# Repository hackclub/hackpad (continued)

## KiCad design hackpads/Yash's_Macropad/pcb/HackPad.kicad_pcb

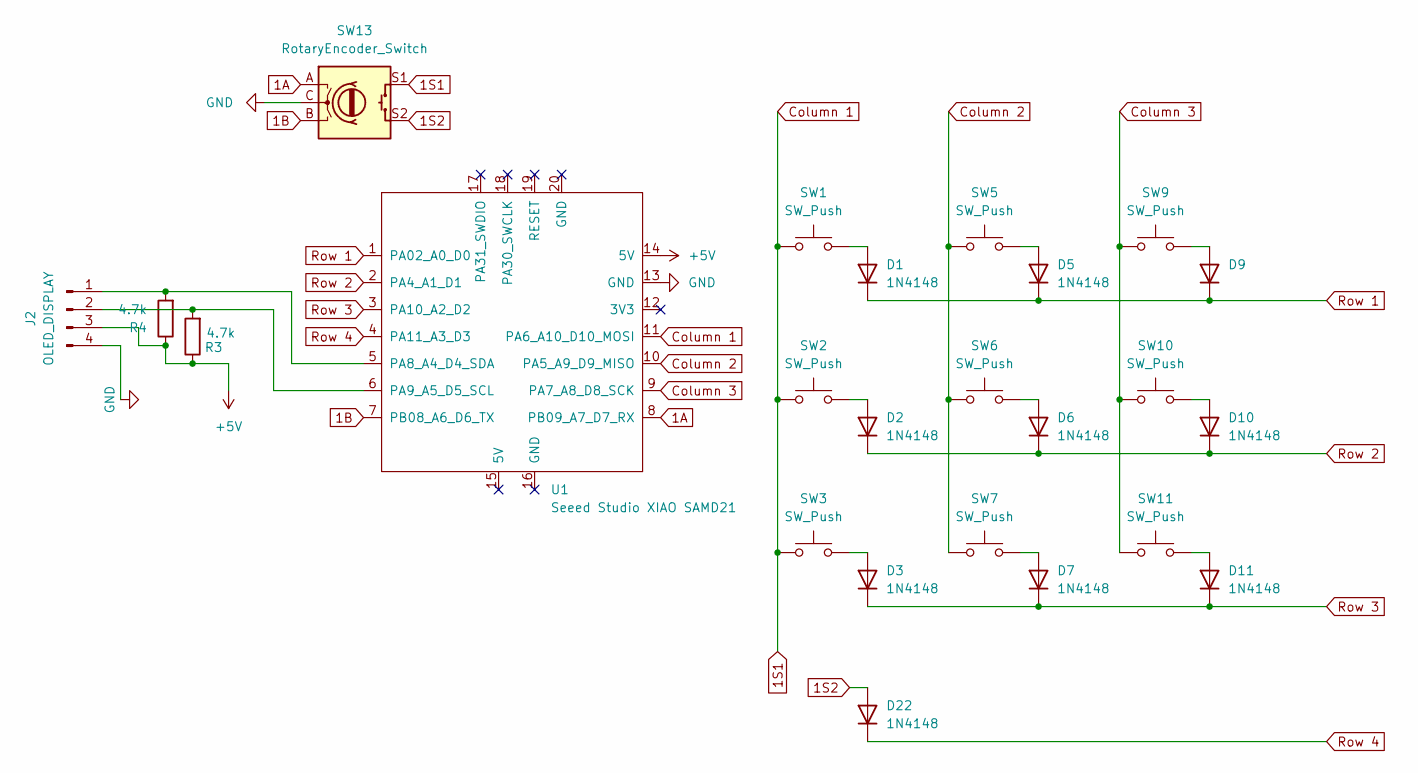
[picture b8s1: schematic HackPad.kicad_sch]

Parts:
D1, D2, D3, D5, D6, D7, D9, D10, D11, D22: 1N4148; D_DO-35_SOD27_P7.62mm_Horizontal
J2: OLED_DISPLAY; 0.91_3D
R3, R4: 4.7k; R_Axial_DIN0204_L3.6mm_D1.6mm_P5.08mm_Horizontal
SW1, SW2, SW3, SW5, SW6, SW7, SW9, SW10, SW11: SW_Push; Cherry_MX_1.00u_PCB
SW13: RotaryEncoder_Switch; RotaryEncoder_Alps_EC11E-Switch_Vertical_H20mm_3D
U1: Seeed Studio XIAO SAMD21; XIAO-Generic-Thruhole-14P-2.54-21X17.8MM

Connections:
1A: SW13.A, U1.8 (PB09_A7_D7_RX)
1B: SW13.B, U1.7 (PB08_A6_D6_TX)
1S1: SW1.1, SW2.1, SW3.1, SW13.S1, U1.11 (PA6_A10_D10_MOSI)
1S2: D22.2 (A), SW13.S2
+5V: J2.3, R3.1, R4.1, U1.14 (5V)
Column 2: SW5.1, SW6.1, SW7.1, U1.10 (PA5_A9_D9_MISO)
Column 3: SW9.1, SW10.1, SW11.1, U1.9 (PA7_A8_D8_SCK)
GND: J2.4, SW13.C, U1.13 (GND)
unnamed: D1.2 (A), SW1.2
unnamed: D2.2 (A), SW2.2
unnamed: D3.2 (A), SW3.2
unnamed: D5.2 (A), SW5.2
unnamed: D6.2 (A), SW6.2
unnamed: D7.2 (A), SW7.2
unnamed: D9.2 (A), SW9.2
unnamed: D10.2 (A), SW10.2
unnamed: D11.2 (A), SW11.2
unnamed: J2.1, R4.2, U1.5 (PA8_A4_D4_SDA)
unnamed: J2.2, R3.2, U1.6 (PA9_A5_D5_SCL)
Row 1: D1.1 (K), D5.1 (K), D9.1 (K), U1.1 (PA02_A0_D0)
Row 2: D2.1 (K), D6.1 (K), D10.1 (K), U1.2 (PA4_A1_D1)
Row 3: D3.1 (K), D7.1 (K), D11.1 (K), U1.3 (PA10_A2_D2)
Row 4: D22.1 (K), U1.4 (PA11_A3_D3)

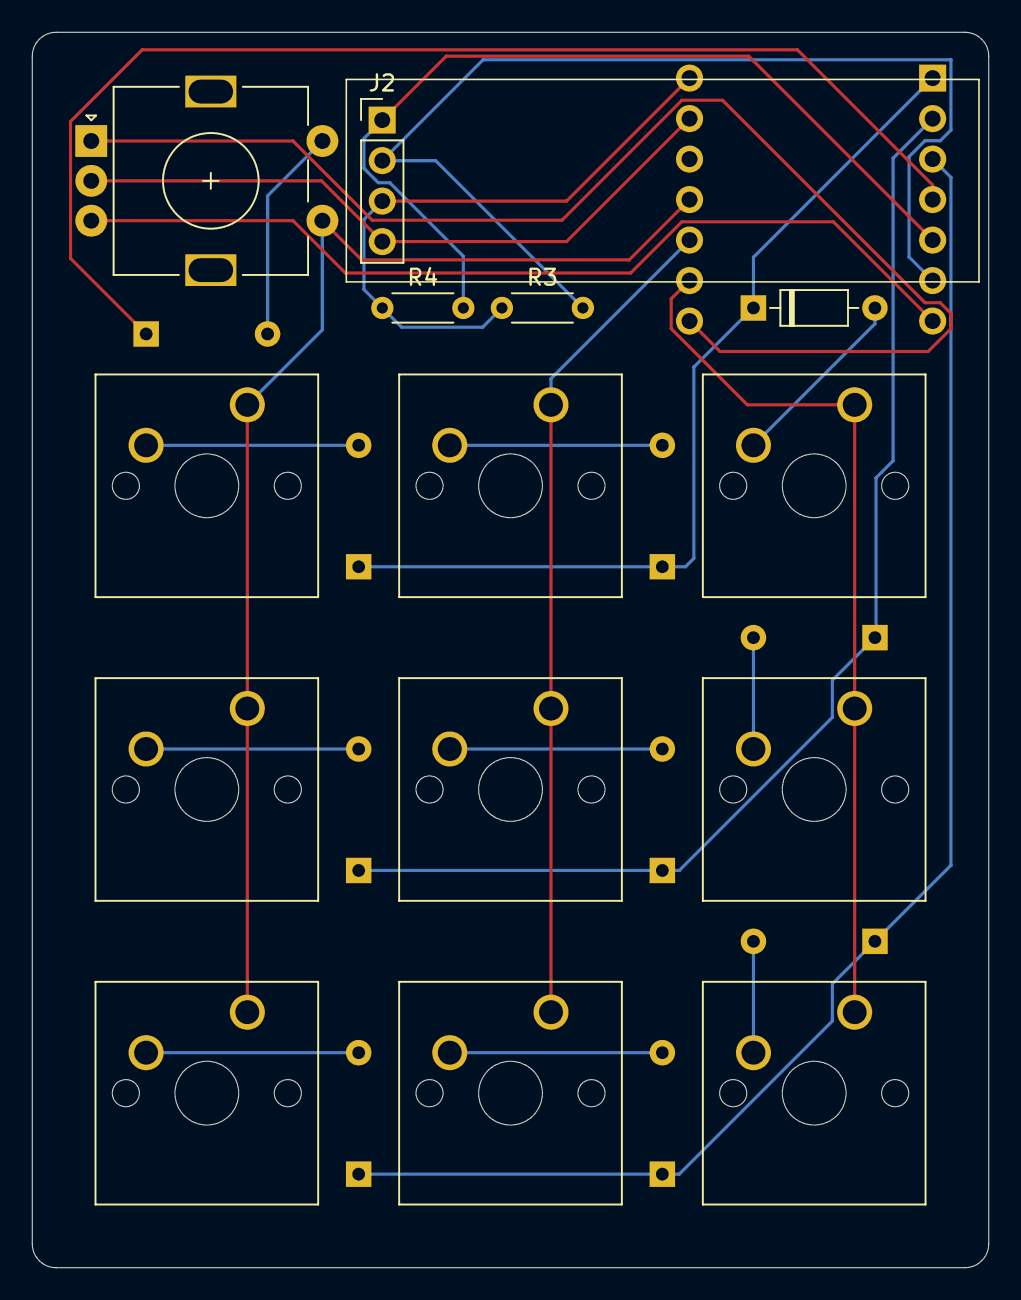
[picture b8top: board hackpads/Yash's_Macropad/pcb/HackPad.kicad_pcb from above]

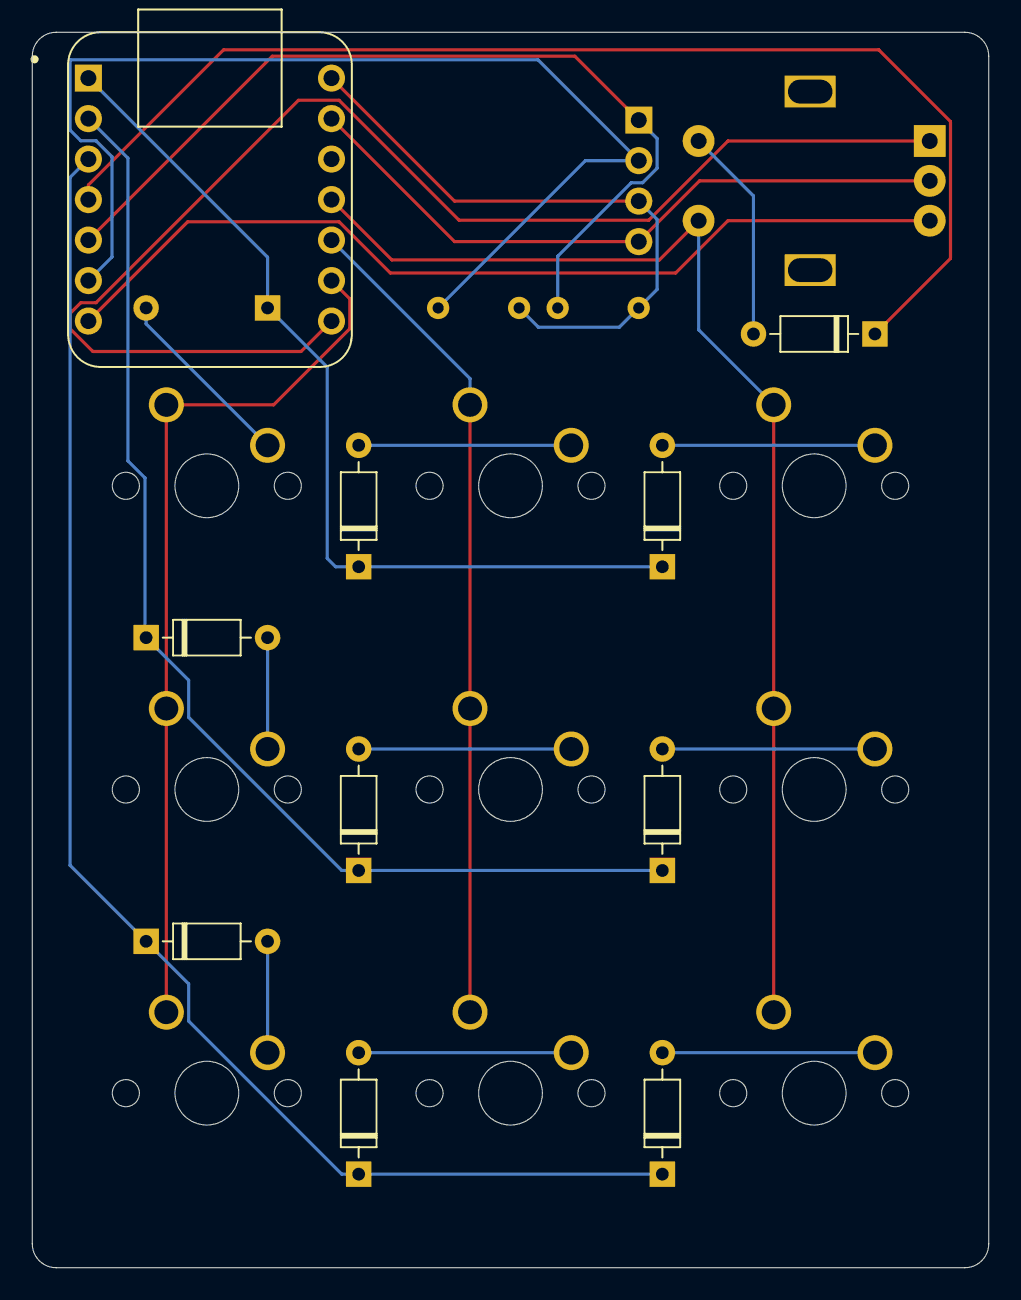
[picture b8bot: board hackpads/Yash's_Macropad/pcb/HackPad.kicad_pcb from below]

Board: 2 copper layers, 60.0 x 77.5 mm, 24 parts (10 on the bottom side), 23 nets.
